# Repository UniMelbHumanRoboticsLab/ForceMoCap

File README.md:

# ForceMoCap
System Development for measuring subject joint angle, task position tracking and human-environment interaction forces.

## [Force Tracking System](https://github.com/UniMelbHumanRoboticsLab/ForceMoCap/tree/main/force_tracking) - `force_tracking`
- Force Tracking Glove Hardware Design Doc and Firmware for collecting interaction force between human and environment.

## [Motion Capture System](https://github.com/UniMelbHumanRoboticsLab/ForceMoCap/tree/main/mo_cap)  - `mo_cap`
- Motion Capture SDKs
    - XSENS - upper body joint angles and communication codes
    - OpenVR and OpenSDK - position tracking / hand kinematic tracking and communication codes

## [Upper Limb DH Model](https://github.com/UniMelbHumanRoboticsLab/ForceMoCap/tree/main/isbul_pckg)  - `isbul_pckg`
- DH Model compatible with [XSENS Biomechanical Model](https://base.movella.com/s/article/MVN-Biomechanical-Model?language=en_US) and [ISB Biomechanical Model](https://www.sciencedirect.com/science/article/pii/S002192900400301X?via%3Dihub) up to 12 DOFs.

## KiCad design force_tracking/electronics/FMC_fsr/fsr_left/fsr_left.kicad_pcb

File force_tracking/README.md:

# Force Tracking System - `force_tracking`
Force/Position Tracking Gloves Hardware Design and Firmware Packages for collecting interaction force between human and environment (Note that data acquisition APIs are located in `mo_cap`).

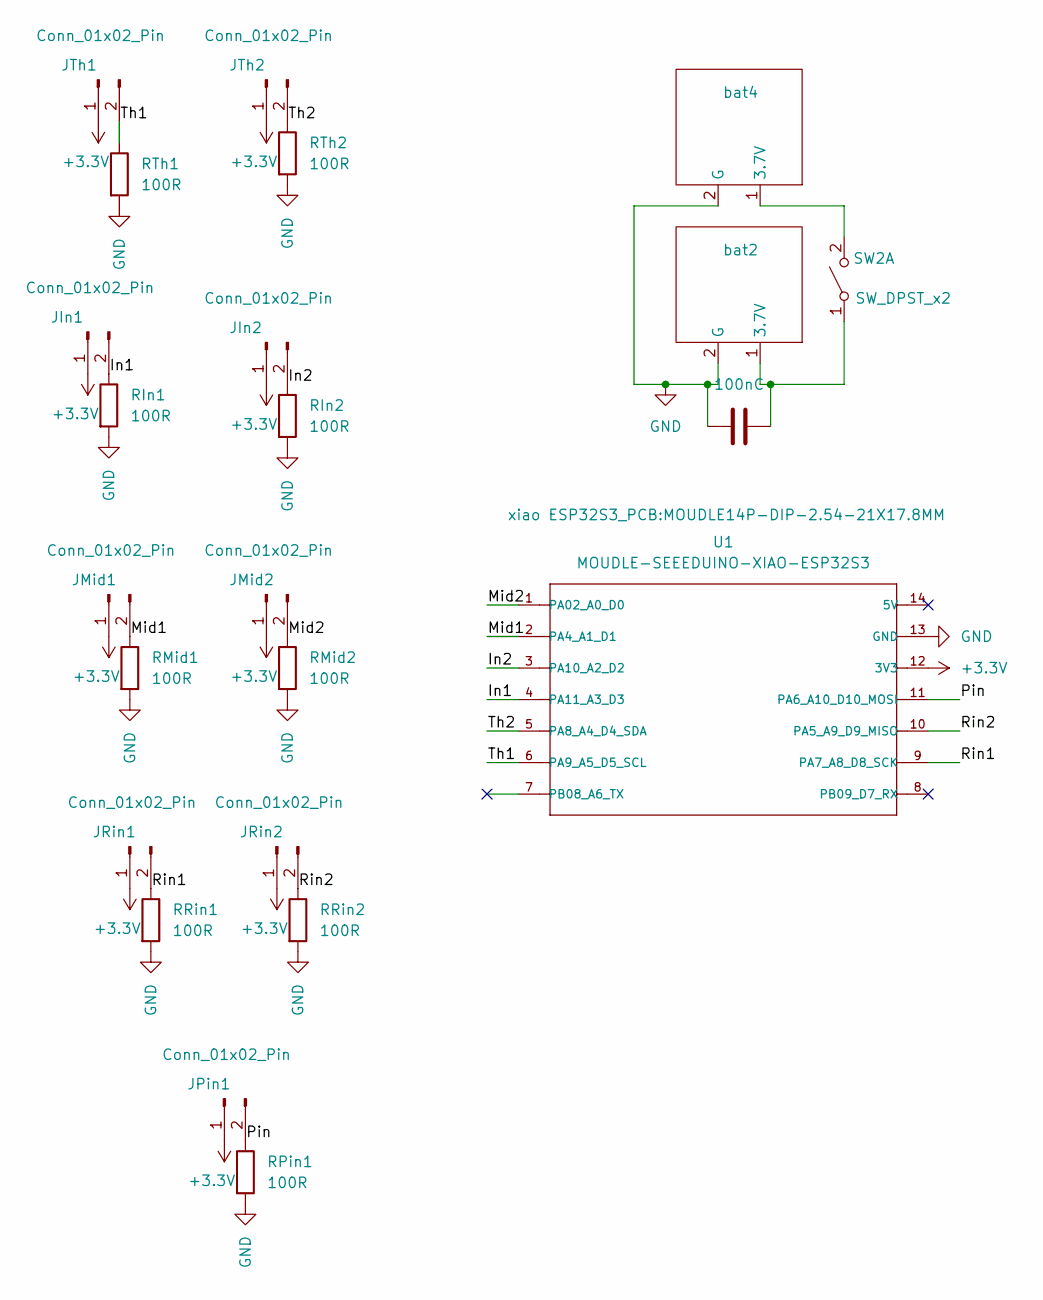
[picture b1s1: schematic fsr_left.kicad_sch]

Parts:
C2: 100nC; C_Disc_D3.0mm_W2.0mm_P2.50mm
JIn1, JIn2: Conn_01x02_Pin; JST_XH_S2B-XH-A_1x02_P2.50mm_Horizontal
JMid1, JMid2: Conn_01x02_Pin; JST_XH_S2B-XH-A_1x02_P2.50mm_Horizontal
JPin1: Conn_01x02_Pin; JST_XH_S2B-XH-A_1x02_P2.50mm_Horizontal
JRin1, JRin2: Conn_01x02_Pin; JST_XH_S2B-XH-A_1x02_P2.50mm_Horizontal
JTh1, JTh2: Conn_01x02_Pin; JST_XH_S2B-XH-A_1x02_P2.50mm_Horizontal
RIn1, RIn2: 100R; R_Axial_DIN0204_L3.6mm_D1.6mm_P1.90mm_Vertical
RMid1, RMid2: 100R; R_Axial_DIN0204_L3.6mm_D1.6mm_P1.90mm_Vertical
RPin1: 100R; R_Axial_DIN0204_L3.6mm_D1.6mm_P1.90mm_Vertical
RRin1, RRin2: 100R; R_Axial_DIN0204_L3.6mm_D1.6mm_P1.90mm_Vertical
RTh1, RTh2: 100R; R_Axial_DIN0204_L3.6mm_D1.6mm_P1.90mm_Vertical
SW2: SW_DPST_x2; JST_PH_B2B-PH-K_1x02_P2.00mm_Vertical
U1: MOUDLE-SEEEDUINO-XIAO-ESP32S3; MOUDLE14P-DIP-2.54-21X17.8MM
bat2, bat4: JST_PH_B2B-PH-K_1x02_P2.00mm_Vertical

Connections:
+3.3V: JIn1.1, JIn2.1, JMid1.1, JMid2.1, JPin1.1, JRin1.1, JRin2.1, JTh1.1, JTh2.1, U1.12 (3V3)
/In1: JIn1.2, RIn1.1, U1.4 (PA11_A3_D3)
/In2: JIn2.2, RIn2.1, U1.3 (PA10_A2_D2)
/Mid1: JMid1.2, RMid1.1, U1.2 (PA4_A1_D1)
/Mid2: JMid2.2, RMid2.1, U1.1 (PA02_A0_D0)
/Pin: JPin1.2, RPin1.1, U1.11 (PA6_A10_D10_MOSI)
/Rin1: JRin1.2, RRin1.1, U1.9 (PA7_A8_D8_SCK)
/Rin2: JRin2.2, RRin2.1, U1.10 (PA5_A9_D9_MISO)
/Th1: JTh1.2, RTh1.1, U1.6 (PA9_A5_D5_SCL)
/Th2: JTh2.2, RTh2.1, U1.5 (PA8_A4_D4_SDA)
GND: C2.2, RIn1.2, RIn2.2, RMid1.2, RMid2.2, RPin1.2, RRin1.2, RRin2.2, RTh1.2, RTh2.2, U1.13 (GND), bat2.2 (G), bat4.2 (G)
unnamed: C2.1, SW2.1 (A), bat2.1 (3.7V)
unnamed: SW2.2 (B), bat4.1 (3.7V)

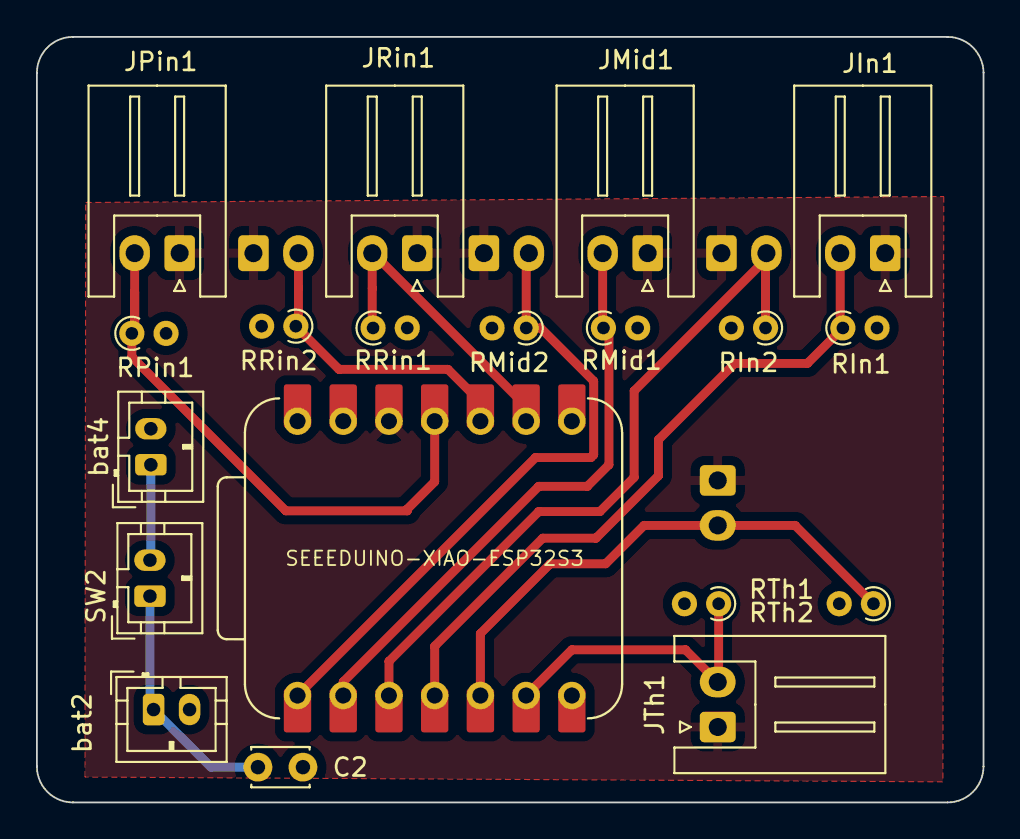
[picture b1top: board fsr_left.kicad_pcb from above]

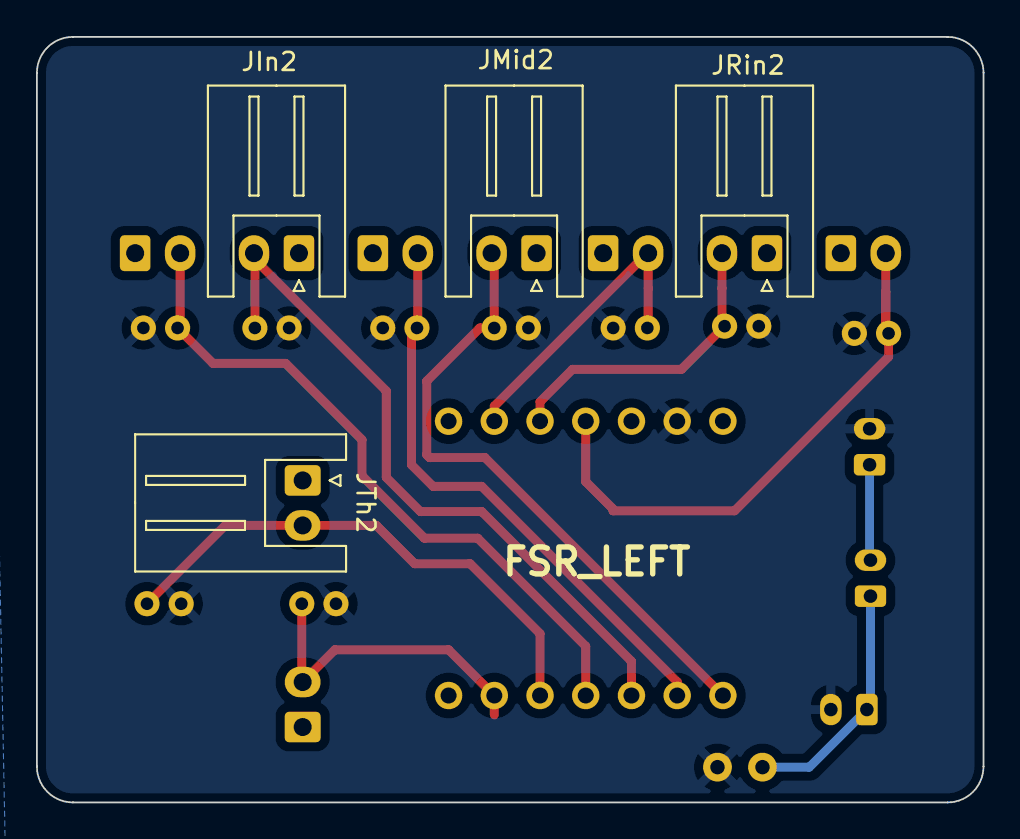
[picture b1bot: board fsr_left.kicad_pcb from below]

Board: 2 copper layers, 52.6 x 42.5 mm, 23 parts (4 on the bottom side), 13 nets.

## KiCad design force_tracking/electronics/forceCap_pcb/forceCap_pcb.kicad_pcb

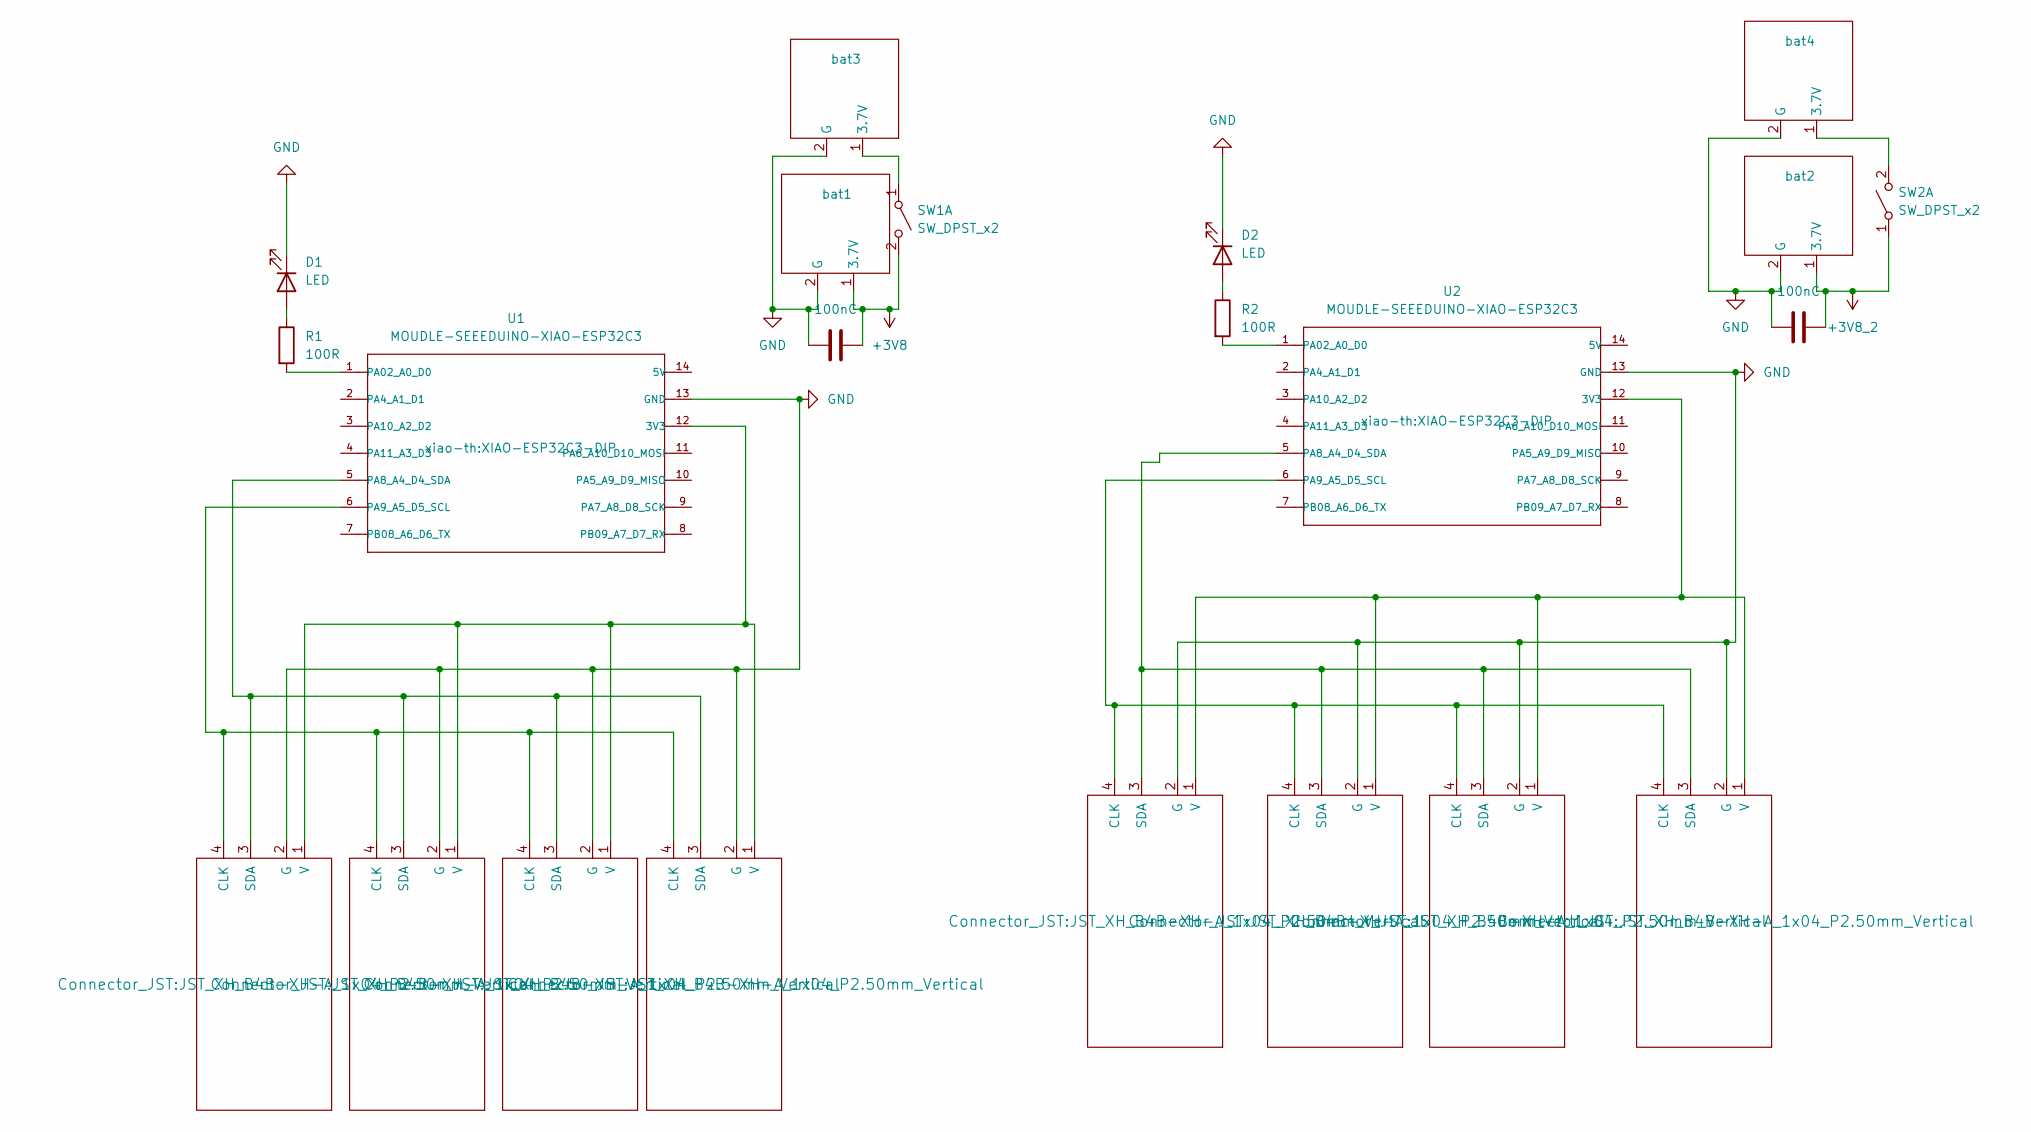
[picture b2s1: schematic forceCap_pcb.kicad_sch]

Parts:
C1, C2: 100nC; CP_Radial_D5.0mm_P2.50mm
D1, D2: LED; LED_D3.0mm
IC1, IC2, IC3, IC4, IC5, IC6, IC7, IC8: MLX90393; JST_XH_B4B-XH-A_1x04_P2.50mm_Vertical
R1, R2: 100R; R_Axial_DIN0204_L3.6mm_D1.6mm_P1.90mm_Vertical
SW1, SW2: SW_DPST_x2; JST_PH_B2B-PH-K_1x02_P2.00mm_Vertical
U1, U2: MOUDLE-SEEEDUINO-XIAO-ESP32C3; XIAO-ESP32C3-DIP
bat1, bat2, bat3, bat4: JST_PH_B2B-PH-K_1x02_P2.00mm_Vertical

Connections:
+3V8: C1.1, SW1.2 (B), bat1.1 (3.7V)
+3V8_2: C2.1, SW2.1 (A), bat2.1 (3.7V)
GND: C1.2, C2.2, D1.1 (K), D2.1 (K), IC1.2 (G), IC2.2 (G), IC3.2 (G), IC4.2 (G), IC5.2 (G), IC6.2 (G), IC7.2 (G), IC8.2 (G), U1.13 (GND), U2.13 (GND), bat1.2 (G), bat2.2 (G), bat3.2 (G), bat4.2 (G)
unnamed: D1.2 (A), R1.1
unnamed: D2.2 (A), R2.1
unnamed: IC1.4 (CLK), IC2.4 (CLK), IC3.4 (CLK), IC4.4 (CLK), U1.6 (PA9_A5_D5_SCL)
unnamed: IC1.3 (SDA), IC2.3 (SDA), IC3.3 (SDA), IC4.3 (SDA), U1.5 (PA8_A4_D4_SDA)
unnamed: IC1.1 (V), IC2.1 (V), IC3.1 (V), IC4.1 (V), U1.12 (3V3)
unnamed: IC5.4 (CLK), IC6.4 (CLK), IC7.4 (CLK), IC8.4 (CLK), U2.6 (PA9_A5_D5_SCL)
unnamed: IC5.3 (SDA), IC6.3 (SDA), IC7.3 (SDA), IC8.3 (SDA), U2.5 (PA8_A4_D4_SDA)
unnamed: IC5.1 (V), IC6.1 (V), IC7.1 (V), IC8.1 (V), U2.12 (3V3)
unnamed: SW1.1 (A), bat3.1 (3.7V)
unnamed: SW2.2 (B), bat4.1 (3.7V)
unnamed: R1.2, U1.1 (PA02_A0_D0)
unnamed: R2.2, U2.1 (PA02_A0_D0)

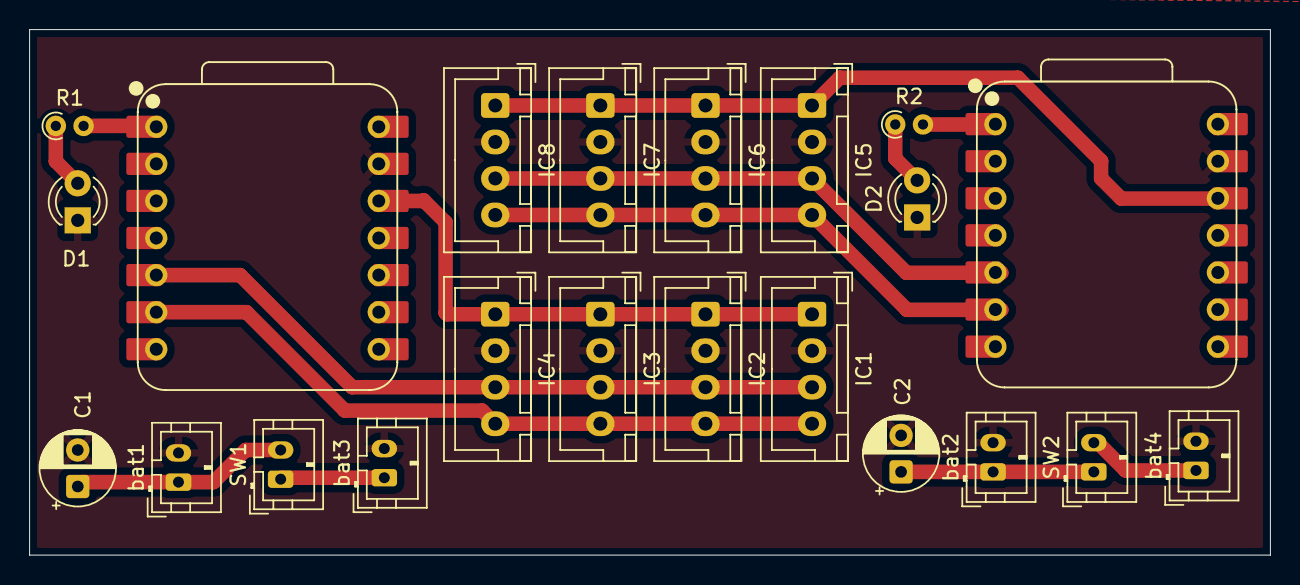
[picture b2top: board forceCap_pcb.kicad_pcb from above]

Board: 4 copper layers, 85.0 x 36.0 mm, 22 parts (0 on the bottom side), 15 nets.

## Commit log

2024-12-04 initial update
2024-12-04 requirement.txt
2024-12-04 checks
2024-12-05 example requirements list
2024-12-05 update device requirements and documentation
2024-12-10 change udp to tcp
2024-12-10 update examples
2024-12-19 update arm model
2025-01-09 cad files
2025-04-08 backup
2025-06-24 major update
2025-06-24 fmc readme update
2025-06-24 gitignore minor update
2025-06-24 create pyrft
    add pyrft
2025-09-16 huge update
    sorry cant keep track of all of it
2025-10-01 huge update
2025-10-07 first complete development version complete!
2025-10-07 auto-scale and manual scale
    add_live_stream_plot to allow auto scale or manual setting for highest range
2025-10-08 sanity updates for exp1
    last minute sanity updates for experiment 1
2025-10-09 hand ruler
    measure hand lengths
2025-10-09 experiment 1 adjustments
2025-10-09 preliminary analysis code
2025-10-10 analysis code update
